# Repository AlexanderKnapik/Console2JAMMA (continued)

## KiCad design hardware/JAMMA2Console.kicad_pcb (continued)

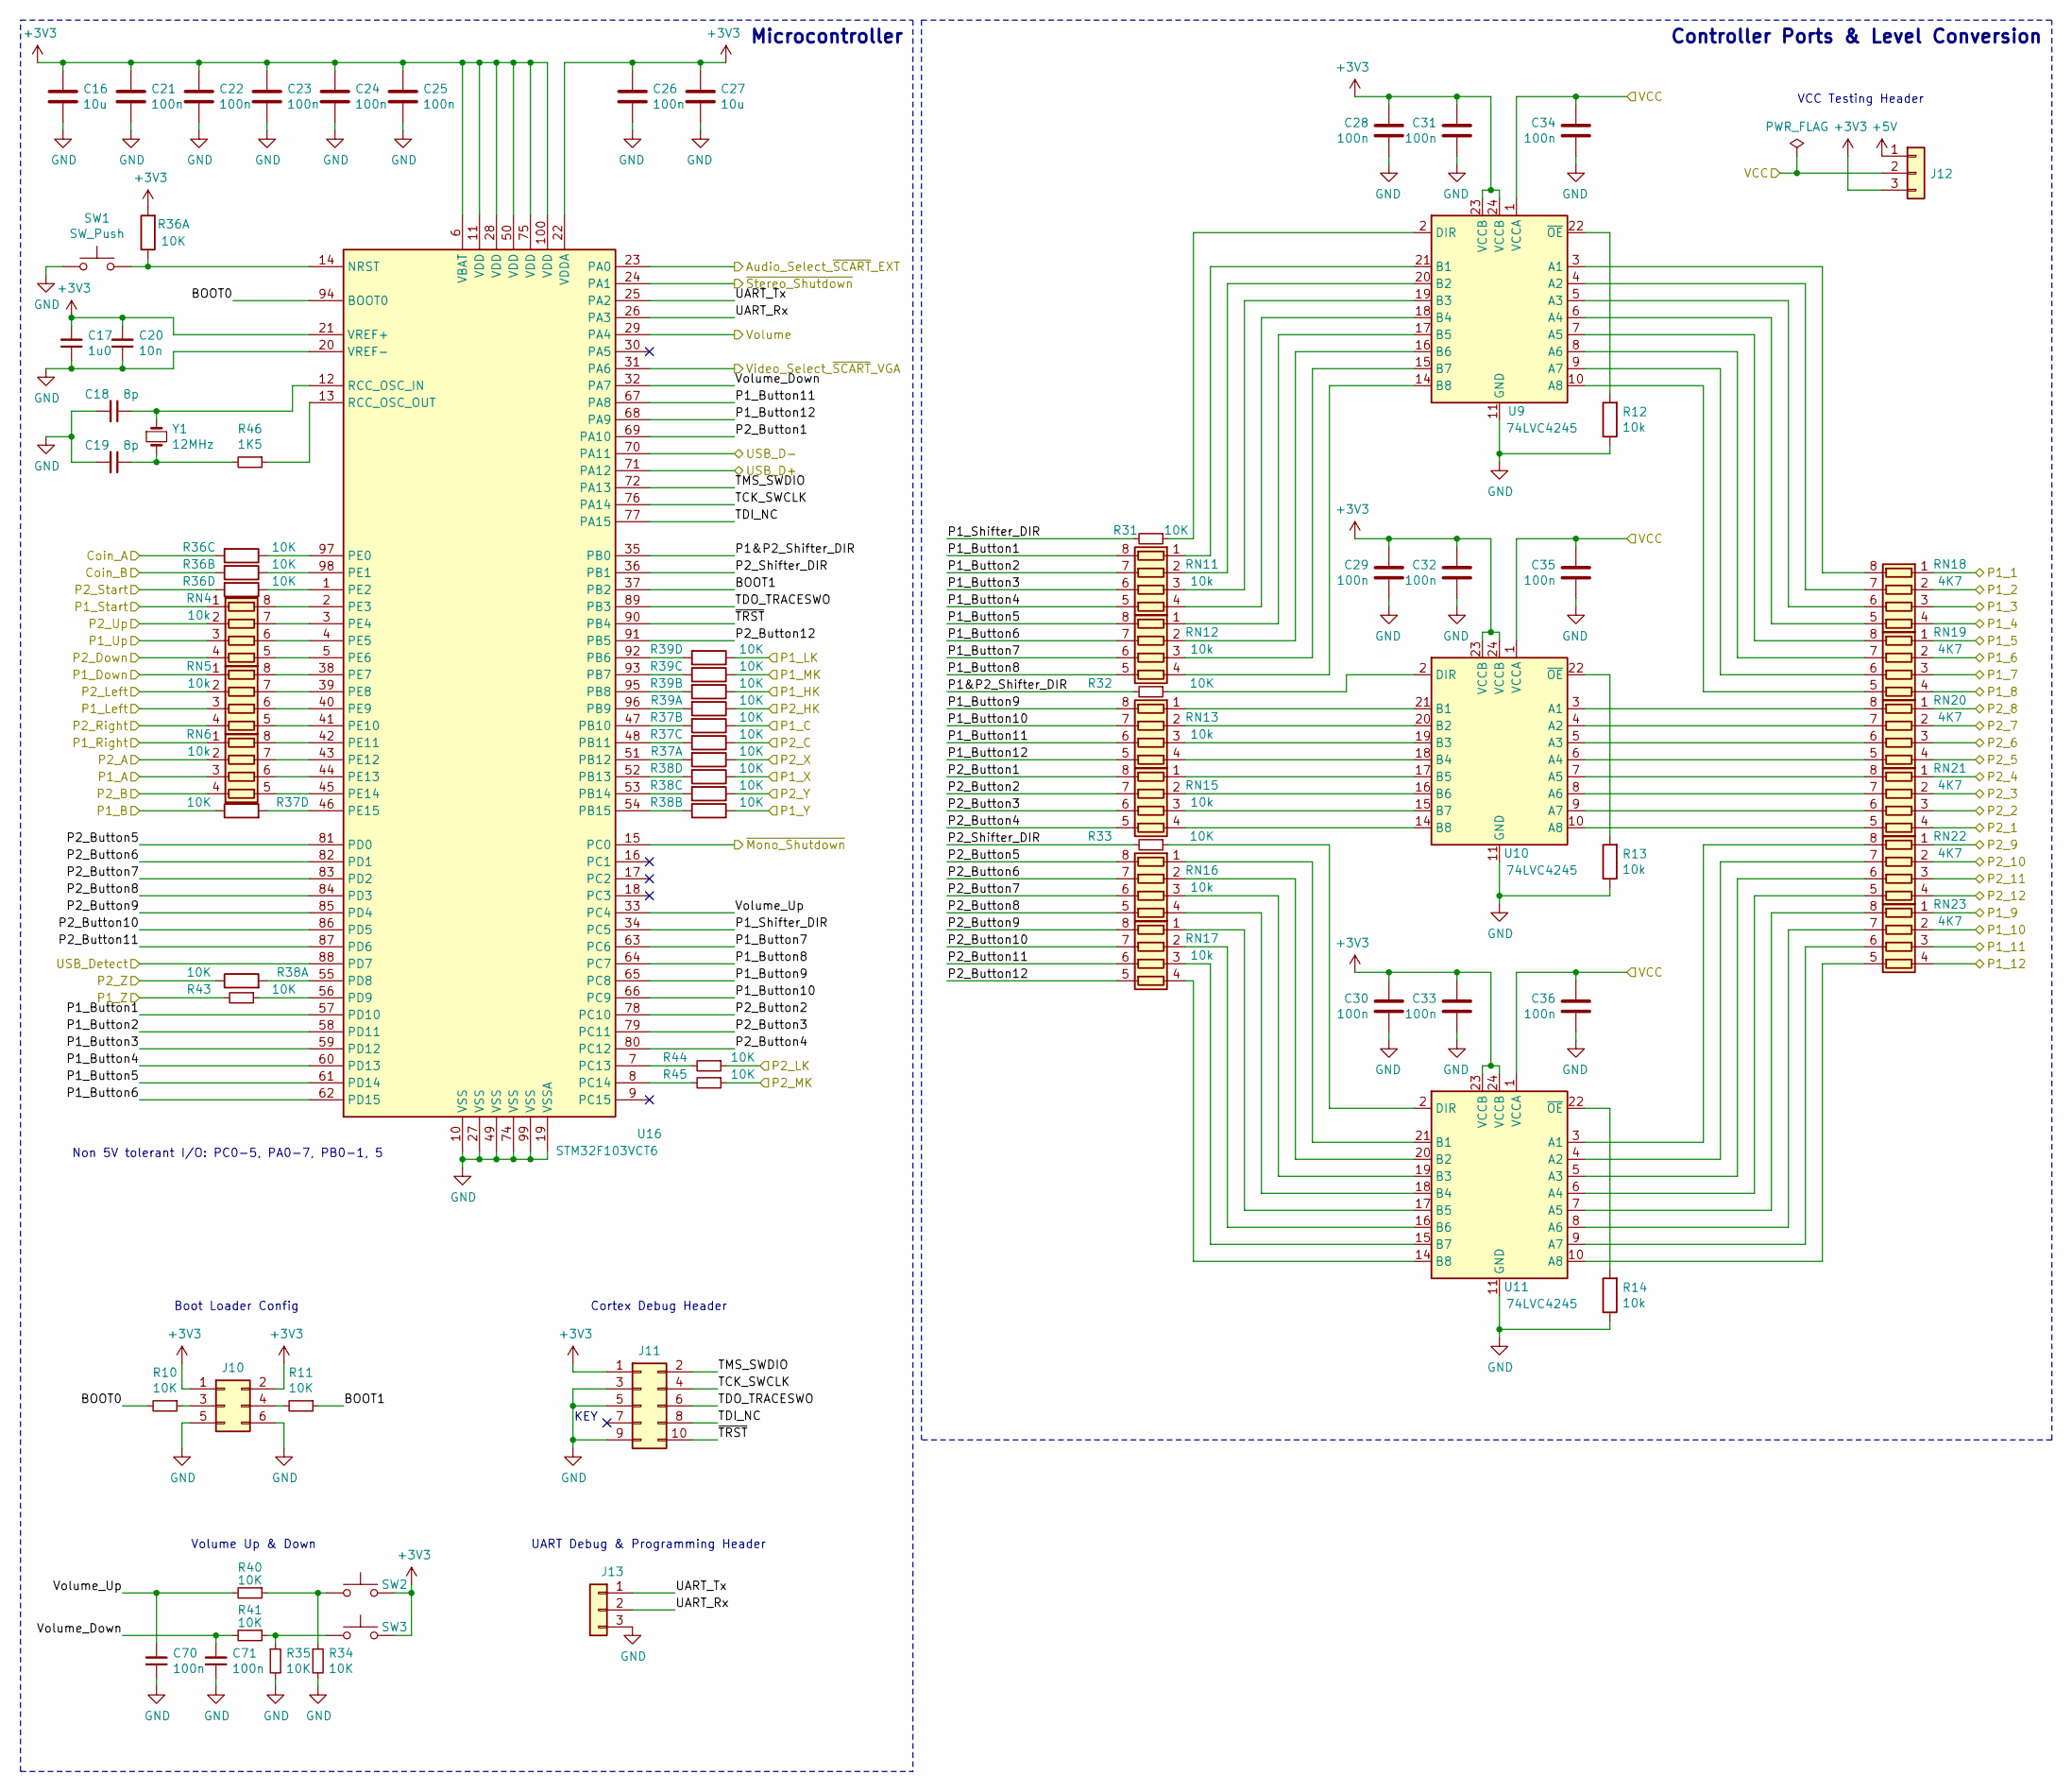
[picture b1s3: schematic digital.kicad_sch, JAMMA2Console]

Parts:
C16, C27: 10u; C_0805_2012Metric
C17: 1u0; C_0603_1608Metric
C18, C19: 8p; C_0603_1608Metric
C20: 10n; C_0603_1608Metric
C21, C22, C23, C24, C25, C26, C28, C29, C30, C31, C32, C33, C34, C35, C36, C70, C71: 100n; C_0603_1608Metric
J10: Conn_02x03_Odd_Even; PinHeader_2x03_P2.54mm_Vertical_SMD
J11: Conn_02x05_Odd_Even; PinHeader_2x05_P1.27mm_Vertical_SMD
J12, J13: Conn_01x03; PinHeader_1x03_P2.54mm_Vertical
R10, R11, R31, R32, R33, R34, R35, R40, R41, R43, R44, R45: 10K; R_0603_1608Metric
R12, R13, R14: 10k; R_0603_1608Metric
R36, R37, R38, R39: 10K; R_Array_Convex_4x0603
R46: 1K5; R_0603_1608Metric
RN4, RN5, RN6, RN11, RN12, RN13, RN15, RN16, RN17: 10k; R_Array_Convex_4x0603
RN18, RN19, RN20, RN21, RN22, RN23: 4K7; R_Array_Convex_4x0603
SW1, SW2, SW3: SW_Push; SW_Push_SPST_NO_Alps_SKRP
U9, U10, U11: 74LVC4245; TSSOP-24_4.4x7.8mm_P0.65mm
U16: STM32F103VCT6; LQFP-100_14x14mm_P0.5mm
Y1: 12MHz; Crystal_SMD_5032-2Pin_5.0x3.2mm

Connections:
+3V3: C16.1, C17.2, C20.2, C21.1, C22.1, C23.1, C24.1, C25.1, C26.1, C27.1, C28.1, C29.1, C30.1, C31.1, C32.1, C33.1, J10.1, J10.2, J11.1, J12.3, R36.1, SW2.2, SW3.2, U9.23 (VCCB), U9.24 (VCCB), U10.23 (VCCB), U10.24 (VCCB), U11.23 (VCCB), U11.24 (VCCB), U16.6 (VBAT), U16.11 (VDD), U16.21 (VREF+), U16.22 (VDDA), U16.28 (VDD), U16.50 (VDD), U16.75 (VDD), U16.100 (VDD); also elsewhere on the board
+5V: J12.1; also elsewhere on the board
/Audio_Select_~SCART~_EXT: U16.23 (PA0); also elsewhere on the board
/Coin_A: R36.3; also elsewhere on the board
/Coin_B: R36.2; also elsewhere on the board
/Digital I/O/BOOT0: R10.2, U16.94 (BOOT0)
/Digital I/O/BOOT1: R11.1, U16.37 (PB2)
/Digital I/O/P1&P2_Shifter_DIR: R32.2, U16.35 (PB0)
/Digital I/O/P1_Button1: RN11.8 (R1.2), U16.57 (PD10)
/Digital I/O/P1_Button2: RN11.7 (R2.2), U16.58 (PD11)
/Digital I/O/P1_Button3: RN11.6 (R3.2), U16.59 (PD12)
/Digital I/O/P1_Button4: RN11.5 (R4.2), U16.60 (PD13)
/Digital I/O/P1_Button5: RN12.8 (R1.2), U16.61 (PD14)
/Digital I/O/P1_Button6: RN12.7 (R2.2), U16.62 (PD15)
/Digital I/O/P1_Button7: RN12.6 (R3.2), U16.63 (PC6)
/Digital I/O/P1_Button8: RN12.5 (R4.2), U16.64 (PC7)
/Digital I/O/P1_Button9: RN13.8 (R1.2), U16.65 (PC8)
/Digital I/O/P1_Button10: RN13.7 (R2.2), U16.66 (PC9)
/Digital I/O/P1_Button11: RN13.6 (R3.2), U16.67 (PA8)
/Digital I/O/P1_Button12: RN13.5 (R4.2), U16.68 (PA9)
/Digital I/O/P1_Shifter_DIR: R31.2, U16.34 (PC5)
/Digital I/O/P2_Button1: RN15.8 (R1.2), U16.69 (PA10)
/Digital I/O/P2_Button2: RN15.7 (R2.2), U16.78 (PC10)
/Digital I/O/P2_Button3: RN15.6 (R3.2), U16.79 (PC11)
/Digital I/O/P2_Button4: RN15.5 (R4.2), U16.80 (PC12)
/Digital I/O/P2_Button5: RN16.8 (R1.2), U16.81 (PD0)
/Digital I/O/P2_Button6: RN16.7 (R2.2), U16.82 (PD1)
/Digital I/O/P2_Button7: RN16.6 (R3.2), U16.83 (PD2)
/Digital I/O/P2_Button8: RN16.5 (R4.2), U16.84 (PD3)
/Digital I/O/P2_Button9: RN17.8 (R1.2), U16.85 (PD4)
/Digital I/O/P2_Button10: RN17.7 (R2.2), U16.86 (PD5)
/Digital I/O/P2_Button11: RN17.6 (R3.2), U16.87 (PD6)
/Digital I/O/P2_Button12: RN17.5 (R4.2), U16.91 (PB5)
/Digital I/O/P2_Shifter_DIR: R33.2, U16.36 (PB1)
/Digital I/O/TCK_SWCLK: J11.4, U16.76 (PA14)
/Digital I/O/TDI_NC: J11.8, U16.77 (PA15)
/Digital I/O/TDO_TRACESWO: J11.6, U16.89 (PB3)
/Digital I/O/TMS_SWDIO: J11.2, U16.72 (PA13)
/Digital I/O/UART_Rx: J13.2, U16.26 (PA3)
/Digital I/O/UART_Tx: J13.1, U16.25 (PA2)
/Digital I/O/Volume_Down: C71.2, R41.2, U16.32 (PA7)
/Digital I/O/Volume_Up: C70.2, R40.2, U16.33 (PC4)
/Digital I/O/~TRST~: J11.10, U16.90 (PB4)
/P1_1: RN18.1 (R1.1); also elsewhere on the board
/P1_2: RN18.2 (R2.1); also elsewhere on the board
/P1_3: RN18.3 (R3.1); also elsewhere on the board
/P1_4: RN18.4 (R4.1); also elsewhere on the board
/P1_5: RN19.1 (R1.1); also elsewhere on the board
/P1_6: RN19.2 (R2.1); also elsewhere on the board
/P1_7: RN19.3 (R3.1); also elsewhere on the board
/P1_8: RN19.4 (R4.1); also elsewhere on the board
/P1_9: RN23.1 (R1.1); also elsewhere on the board
/P1_10: RN23.2 (R2.1); also elsewhere on the board
/P1_11: RN23.3 (R3.1); also elsewhere on the board
/P1_12: RN23.4 (R4.1); also elsewhere on the board
/P1_A: RN6.3 (R3.1); also elsewhere on the board
/P1_B: R37.5; also elsewhere on the board
/P1_C: R37.7; also elsewhere on the board
/P1_Down: RN5.1 (R1.1); also elsewhere on the board
/P1_HK: R39.7; also elsewhere on the board
/P1_LK: R39.5; also elsewhere on the board
/P1_Left: RN5.3 (R3.1); also elsewhere on the board
/P1_MK: R39.6; also elsewhere on the board
/P1_Right: RN6.1 (R1.1); also elsewhere on the board
/P1_Start: RN4.1 (R1.1); also elsewhere on the board
/P1_Up: RN4.3 (R3.1); also elsewhere on the board
/P1_X: R38.5; also elsewhere on the board
/P1_Y: R38.7; also elsewhere on the board
/P1_Z: R43.2; also elsewhere on the board
/P2_1: RN21.4 (R4.1); also elsewhere on the board
/P2_2: RN21.3 (R3.1); also elsewhere on the board
/P2_3: RN21.2 (R2.1); also elsewhere on the board
/P2_4: RN21.1 (R1.1); also elsewhere on the board
/P2_5: RN20.4 (R4.1); also elsewhere on the board
/P2_6: RN20.3 (R3.1); also elsewhere on the board
/P2_7: RN20.2 (R2.1); also elsewhere on the board
/P2_8: RN20.1 (R1.1); also elsewhere on the board
/P2_9: RN22.1 (R1.1); also elsewhere on the board
/P2_10: RN22.2 (R2.1); also elsewhere on the board
/P2_11: RN22.3 (R3.1); also elsewhere on the board
/P2_12: RN22.4 (R4.1); also elsewhere on the board
/P2_A: RN6.2 (R2.1); also elsewhere on the board
/P2_B: RN6.4 (R4.1); also elsewhere on the board
/P2_C: R37.6; also elsewhere on the board
/P2_Down: RN4.4 (R4.1); also elsewhere on the board
/P2_HK: R39.8; also elsewhere on the board
/P2_LK: R44.1; also elsewhere on the board
/P2_Left: RN5.2 (R2.1); also elsewhere on the board
/P2_MK: R45.1; also elsewhere on the board
/P2_Right: RN5.4 (R4.1); also elsewhere on the board
/P2_Start: R36.4; also elsewhere on the board
/P2_Up: RN4.2 (R2.1); also elsewhere on the board
/P2_X: R37.8; also elsewhere on the board
/P2_Y: R38.6; also elsewhere on the board
/P2_Z: R38.8; also elsewhere on the board
/USB_D+: U16.71 (PA12); also elsewhere on the board
/USB_D-: U16.70 (PA11); also elsewhere on the board
/USB_Detect: U16.88 (PD7); also elsewhere on the board
/VCC: C34.1, C35.1, C36.1, J12.2, U9.1 (VCCA), U10.1 (VCCA), U11.1 (VCCA); also elsewhere on the board
/Video_Select_~SCART~_VGA: U16.31 (PA6); also elsewhere on the board
/Volume: U16.29 (PA4); also elsewhere on the board
/~Mono_Shutdown~: U16.15 (PC0); also elsewhere on the board
/~Stereo_Shutdown~: U16.24 (PA1); also elsewhere on the board
GND: C16.2, C17.1, C18.2, C19.2, C20.1, C21.2, C22.2, C23.2, C24.2, C25.2, C26.2, C27.2, C28.2, C29.2, C30.2, C31.2, C32.2, C33.2, C34.2, C35.2, C36.2, C70.1, C71.1, J10.5, J10.6, J11.3, J11.5, J11.9, J13.3, R12.1, R13.1, R14.1, R34.2, R35.2, SW1.1, U9.11 (GND), U9.12 (GND), U9.13 (GND), U10.11 (GND), U10.12 (GND), U10.13 (GND), U11.11 (GND), U11.12 (GND), U11.13 (GND), U16.10 (VSS), U16.19 (VSSA), U16.20 (VREF-), U16.27 (VSS), U16.49 (VSS), U16.74 (VSS), U16.99 (VSS); also elsewhere on the board
unnamed: C18.1, U16.12 (RCC_OSC_IN), Y1.1
unnamed: C19.1, R46.2, Y1.2
unnamed: J10.3, R10.1
unnamed: J10.4, R11.2
unnamed: R12.2, U9.22 (~OE)
unnamed: R13.2, U10.22 (~OE)
unnamed: R14.2, U11.22 (~OE)
unnamed: R31.1, U9.2 (DIR)
unnamed: R32.1, U10.2 (DIR)
unnamed: R33.1, U11.2 (DIR)
unnamed: R34.1, R40.1, SW2.1
unnamed: R35.1, R41.1, SW3.1
unnamed: R36.5, U16.1 (PE2)
unnamed: R36.6, U16.97 (PE0)
unnamed: R36.7, U16.98 (PE1)
unnamed: R36.8, SW1.2, U16.14 (NRST)
unnamed: R37.1, U16.51 (PB12)
unnamed: R37.2, U16.47 (PB10)
unnamed: R37.3, U16.48 (PB11)
unnamed: R37.4, U16.46 (PE15)
unnamed: R38.1, U16.55 (PD8)
unnamed: R38.2, U16.54 (PB15)
unnamed: R38.3, U16.53 (PB14)
unnamed: R38.4, U16.52 (PB13)
unnamed: R39.1, U16.96 (PB9)
unnamed: R39.2, U16.95 (PB8)
unnamed: R39.3, U16.93 (PB7)
unnamed: R39.4, U16.92 (PB6)
unnamed: R43.1, U16.56 (PD9)
unnamed: R44.2, U16.7 (PC13)
unnamed: R45.2, U16.8 (PC14)
unnamed: R46.1, U16.13 (RCC_OSC_OUT)
unnamed: RN4.5 (R4.2), U16.5 (PE6)
unnamed: RN4.6 (R3.2), U16.4 (PE5)
unnamed: RN4.7 (R2.2), U16.3 (PE4)
unnamed: RN4.8 (R1.2), U16.2 (PE3)
unnamed: RN5.5 (R4.2), U16.41 (PE10)
unnamed: RN5.6 (R3.2), U16.40 (PE9)
unnamed: RN5.7 (R2.2), U16.39 (PE8)
unnamed: RN5.8 (R1.2), U16.38 (PE7)
unnamed: RN6.5 (R4.2), U16.45 (PE14)
unnamed: RN6.6 (R3.2), U16.44 (PE13)
unnamed: RN6.7 (R2.2), U16.43 (PE12)
unnamed: RN6.8 (R1.2), U16.42 (PE11)
unnamed: RN11.1 (R1.1), U9.21 (B1)
unnamed: RN11.2 (R2.1), U9.20 (B2)
unnamed: RN11.3 (R3.1), U9.19 (B3)
unnamed: RN11.4 (R4.1), U9.18 (B4)
unnamed: RN12.1 (R1.1), U9.17 (B5)
unnamed: RN12.2 (R2.1), U9.16 (B6)
unnamed: RN12.3 (R3.1), U9.15 (B7)
unnamed: RN12.4 (R4.1), U9.14 (B8)
unnamed: RN13.1 (R1.1), U10.21 (B1)
unnamed: RN13.2 (R2.1), U10.20 (B2)
unnamed: RN13.3 (R3.1), U10.19 (B3)
unnamed: RN13.4 (R4.1), U10.18 (B4)
unnamed: RN15.1 (R1.1), U10.17 (B5)
unnamed: RN15.2 (R2.1), U10.16 (B6)
unnamed: RN15.3 (R3.1), U10.15 (B7)
unnamed: RN15.4 (R4.1), U10.14 (B8)
unnamed: RN16.1 (R1.1), U11.21 (B1)
unnamed: RN16.2 (R2.1), U11.20 (B2)
unnamed: RN16.3 (R3.1), U11.19 (B3)
unnamed: RN16.4 (R4.1), U11.18 (B4)
unnamed: RN17.1 (R1.1), U11.17 (B5)
unnamed: RN17.2 (R2.1), U11.16 (B6)
unnamed: RN17.3 (R3.1), U11.15 (B7)
unnamed: RN17.4 (R4.1), U11.14 (B8)
unnamed: RN18.5 (R4.2), U9.6 (A4)
unnamed: RN18.6 (R3.2), U9.5 (A3)
unnamed: RN18.7 (R2.2), U9.4 (A2)
unnamed: RN18.8 (R1.2), U9.3 (A1)
unnamed: RN19.5 (R4.2), U9.10 (A8)
unnamed: RN19.6 (R3.2), U9.9 (A7)
unnamed: RN19.7 (R2.2), U9.8 (A6)
unnamed: RN19.8 (R1.2), U9.7 (A5)
unnamed: RN20.5 (R4.2), U10.6 (A4)
unnamed: RN20.6 (R3.2), U10.5 (A3)
unnamed: RN20.7 (R2.2), U10.4 (A2)
unnamed: RN20.8 (R1.2), U10.3 (A1)
unnamed: RN21.5 (R4.2), U10.10 (A8)
unnamed: RN21.6 (R3.2), U10.9 (A7)
unnamed: RN21.7 (R2.2), U10.8 (A6)
unnamed: RN21.8 (R1.2), U10.7 (A5)
unnamed: RN22.5 (R4.2), U11.6 (A4)
unnamed: RN22.6 (R3.2), U11.5 (A3)
unnamed: RN22.7 (R2.2), U11.4 (A2)
unnamed: RN22.8 (R1.2), U11.3 (A1)
unnamed: RN23.5 (R4.2), U11.10 (A8)
unnamed: RN23.6 (R3.2), U11.9 (A7)
unnamed: RN23.7 (R2.2), U11.8 (A6)
unnamed: RN23.8 (R1.2), U11.7 (A5)

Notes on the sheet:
Non 5V tolerant I/O: PC0-5, PA0-7, PB0-1, 5
Boot Loader Config
Volume Up & Down
UART Debug & Programming Header
Cortex Debug Header
KEY
Microcontroller
VCC Testing Header
Controller Ports & Level Conversion

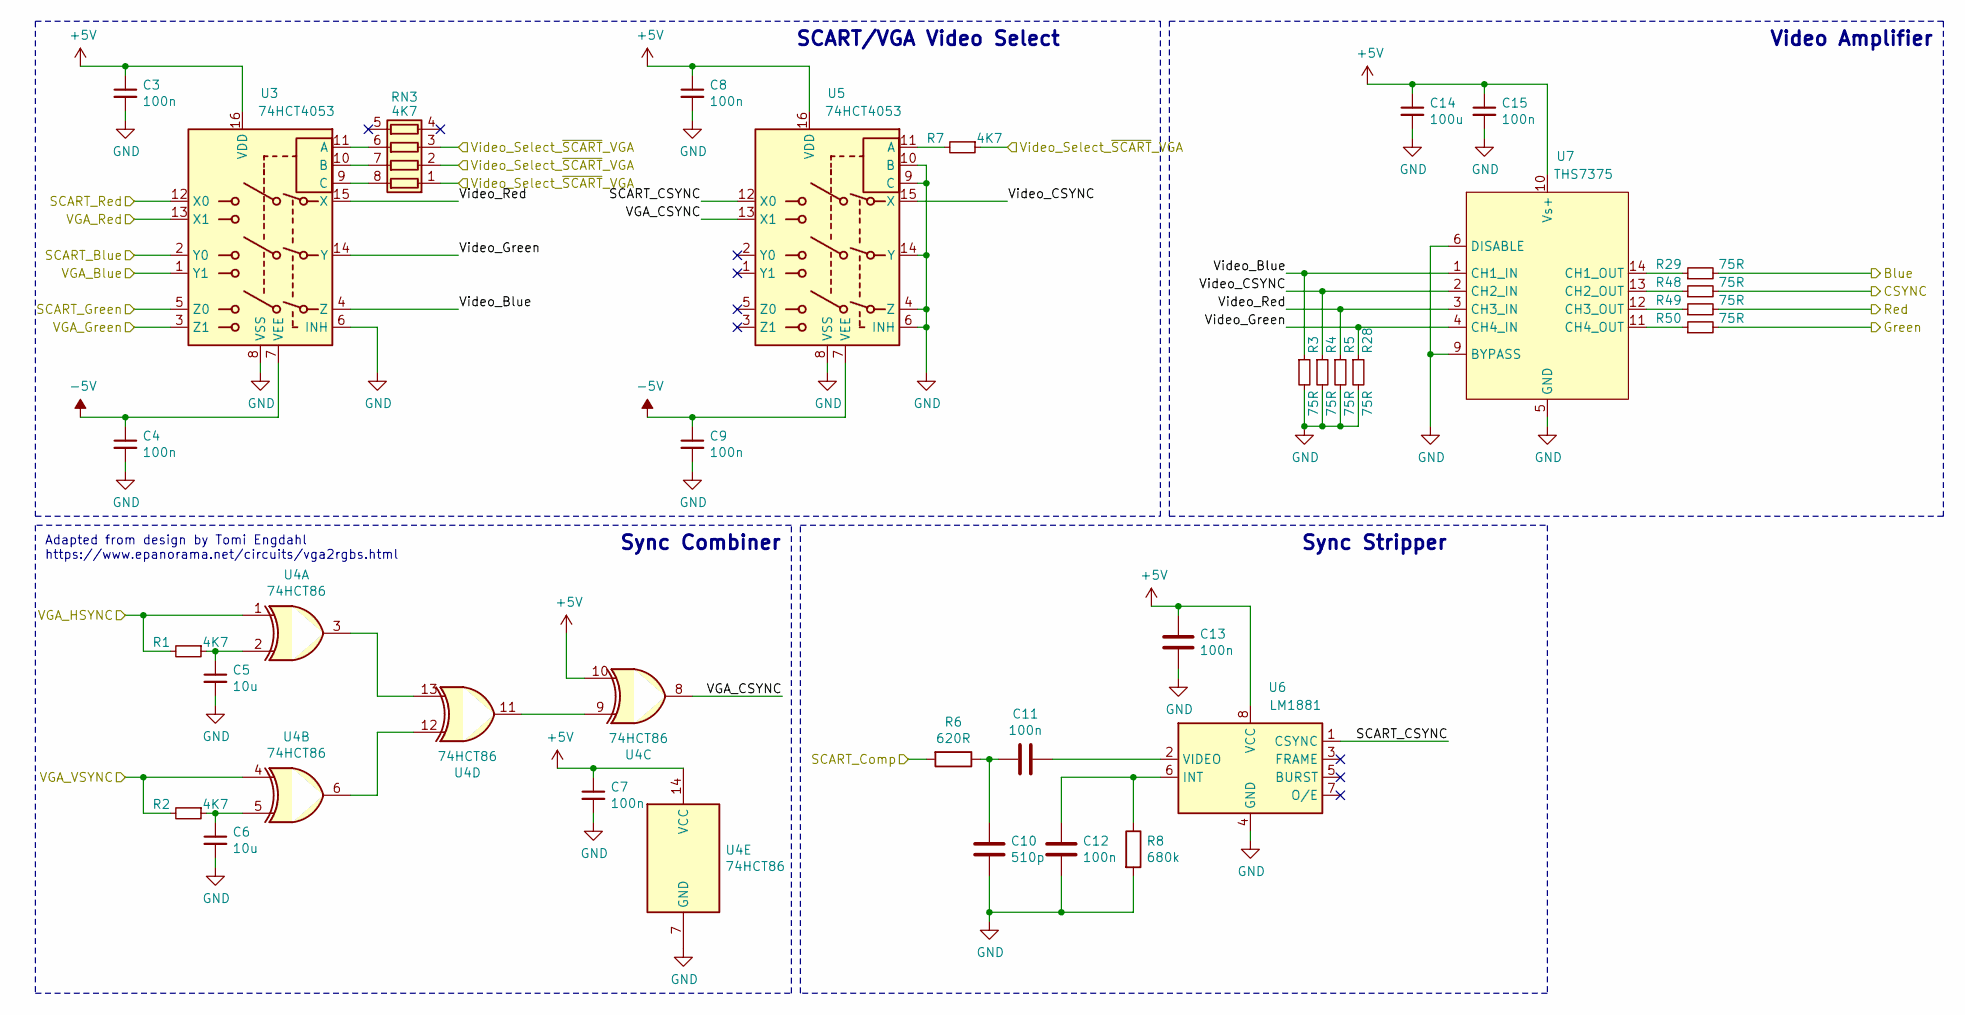
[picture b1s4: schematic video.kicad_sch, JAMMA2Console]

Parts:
C3, C4, C7, C8, C9, C11, C12, C13, C15: 100n; C_0603_1608Metric
C5, C6: 10u; C_0805_2012Metric
C10: 510p; C_0603_1608Metric
C14: 100u; C_1210_3225Metric
R1, R2, R7: 4K7; R_0603_1608Metric
R3, R4, R5, R28, R29, R48, R49, R50: 75R; R_0603_1608Metric
R6: 620R; R_0603_1608Metric
R8: 680k; R_0603_1608Metric
RN3: 4K7; R_Array_Convex_4x0603
U3, U5: 74HCT4053; SSOP-16_5.3x6.2mm_P0.65mm
U4: 74HCT86; SOIC-14_3.9x8.7mm_P1.27mm
U6: LM1881; SOIC-8_3.9x4.9mm_P1.27mm
U7: THS7375; TSSOP-14_4.4x5mm_P0.65mm

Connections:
+5V: C3.1, C7.1, C8.1, C13.1, C14.1, C15.1, U3.16 (VDD), U4.10, U4.14 (VCC), U5.16 (VDD), U6.8 (VCC), U7.10 (Vs+); also elsewhere on the board
-5V: C4.1, C9.1, U3.7 (VEE), U5.7 (VEE); also elsewhere on the board
/Composite_Sync: R48.2; also elsewhere on the board
/SCART_Blue: U3.2 (Y0); also elsewhere on the board
/SCART_Comp: R6.2; also elsewhere on the board
/SCART_Green: U3.5 (Z0); also elsewhere on the board
/SCART_Red: U3.12 (X0); also elsewhere on the board
/VGA_Blue: U3.1 (Y1); also elsewhere on the board
/VGA_Green: U3.3 (Z1); also elsewhere on the board
/VGA_HSYNC: R1.2, U4.1; also elsewhere on the board
/VGA_Red: U3.13 (X1); also elsewhere on the board
/VGA_VSYNC: R2.2, U4.4; also elsewhere on the board
/Video/SCART_CSYNC: U5.12 (X0), U6.1 (CSYNC)
/Video/VGA_CSYNC: U4.8, U5.13 (X1)
/Video/Video_Blue: R3.1, U3.4 (Z), U7.1 (CH1_IN)
/Video/Video_CSYNC: R4.1, U5.15 (X), U7.2 (CH2_IN)
/Video/Video_Green: R28.1, U3.14 (Y), U7.4 (CH4_IN)
/Video/Video_Red: R5.1, U3.15 (X), U7.3 (CH3_IN)
/Video_Blue: R29.2; also elsewhere on the board
/Video_Green: R50.2; also elsewhere on the board
/Video_Red: R49.2; also elsewhere on the board
/Video_Select_~SCART~_VGA: R7.1, RN3.1 (R1.1), RN3.2 (R2.1), RN3.3 (R3.1); also elsewhere on the board
GND: C3.2, C4.2, C5.2, C6.2, C7.2, C8.2, C9.2, C10.2, C12.2, C13.2, C14.2, C15.2, R3.2, R4.2, R5.2, R8.2, R28.2, U3.6 (INH), U3.8 (VSS), U4.7 (GND), U5.4 (Z), U5.6 (INH), U5.8 (VSS), U5.9 (C), U5.10 (B), U5.14 (Y), U6.4 (GND), U7.5 (GND), U7.6 (DISABLE), U7.9 (BYPASS); also elsewhere on the board
unnamed: C5.1, R1.1, U4.2
unnamed: C6.1, R2.1, U4.5
unnamed: C10.1, C11.2, R6.1
unnamed: C11.1, U6.2 (VIDEO)
unnamed: C12.1, R8.1, U6.6 (INT)
unnamed: R7.2, U5.11 (A)
unnamed: R29.1, U7.14 (CH1_OUT)
unnamed: R48.1, U7.13 (CH2_OUT)
unnamed: R49.1, U7.12 (CH3_OUT)
unnamed: R50.1, U7.11 (CH4_OUT)
unnamed: RN3.6 (R3.2), U3.11 (A)
unnamed: RN3.7 (R2.2), U3.10 (B)
unnamed: RN3.8 (R1.2), U3.9 (C)
unnamed: U4.9, U4.11
unnamed: U4.6, U4.12
unnamed: U4.3, U4.13

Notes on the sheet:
Adapted from design by Tomi Engdahl https://www.epanorama.net/circuits/vga2rgbs.html
Sync Combiner
SCART/VGA Video Select
Sync Stripper
Video Amplifier

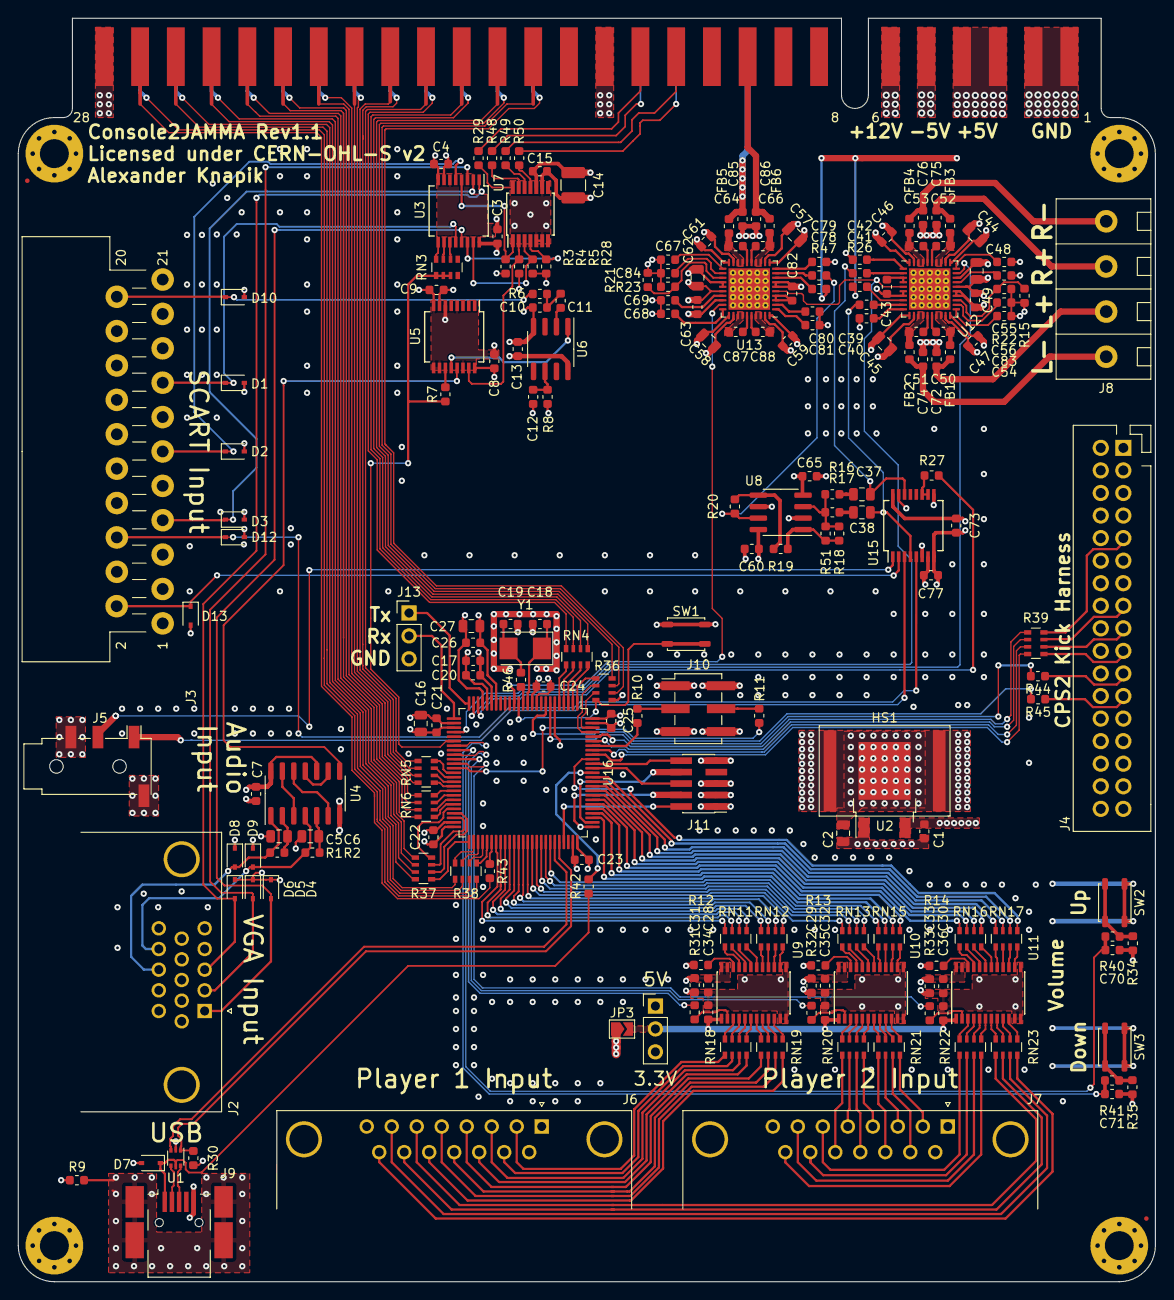
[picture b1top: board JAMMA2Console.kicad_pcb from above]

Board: 4 copper layers, 126.0 x 140.0 mm, 211 parts (0 on the bottom side), 295 nets.

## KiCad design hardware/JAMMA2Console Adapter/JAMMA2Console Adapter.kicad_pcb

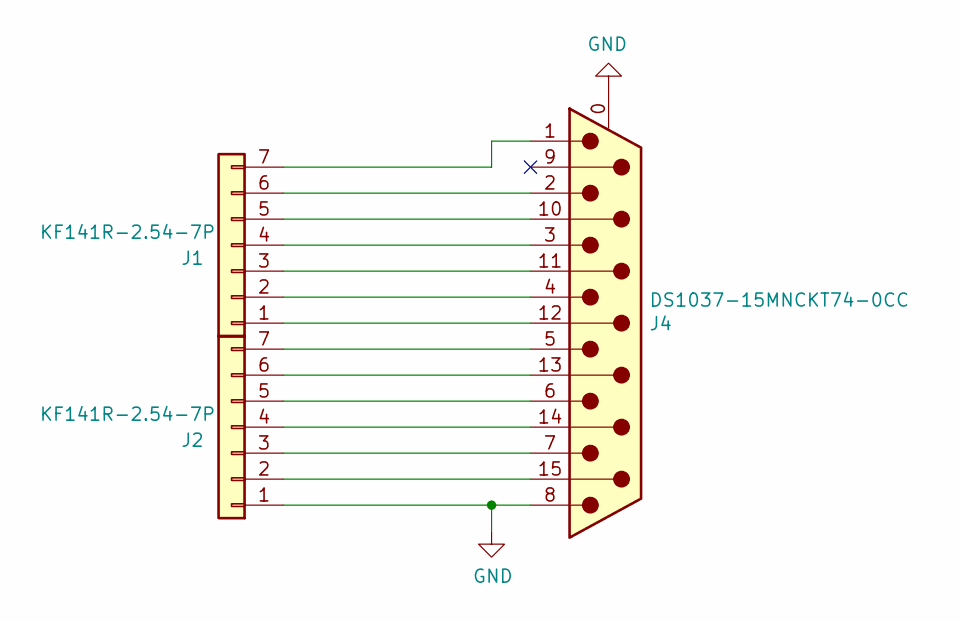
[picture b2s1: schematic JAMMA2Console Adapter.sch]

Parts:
J1, J2: KF141R-2.54-7P; CixiKefa_KF141R-2.54-7P_1x7_P2.54mm_Horizontal
J4: DS1037-15MNCKT74-0CC; DSUB-15_Male_Horizontal_P2.77x2.84mm_EdgePinOffset8.10mm_Ho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

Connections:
GND: J2.1, J4.0 (PAD), J4.8
unnamed: J1.1, J4.12
unnamed: J1.2, J4.4
unnamed: J1.3, J4.11 (P111)
unnamed: J1.4, J4.3
unnamed: J1.5, J4.10
unnamed: J1.6, J4.2
unnamed: J1.7, J4.1
unnamed: J2.2, J4.15
unnamed: J2.3, J4.7
unnamed: J2.4, J4.14
unnamed: J2.5, J4.6
unnamed: J2.6, J4.13
unnamed: J2.7, J4.5

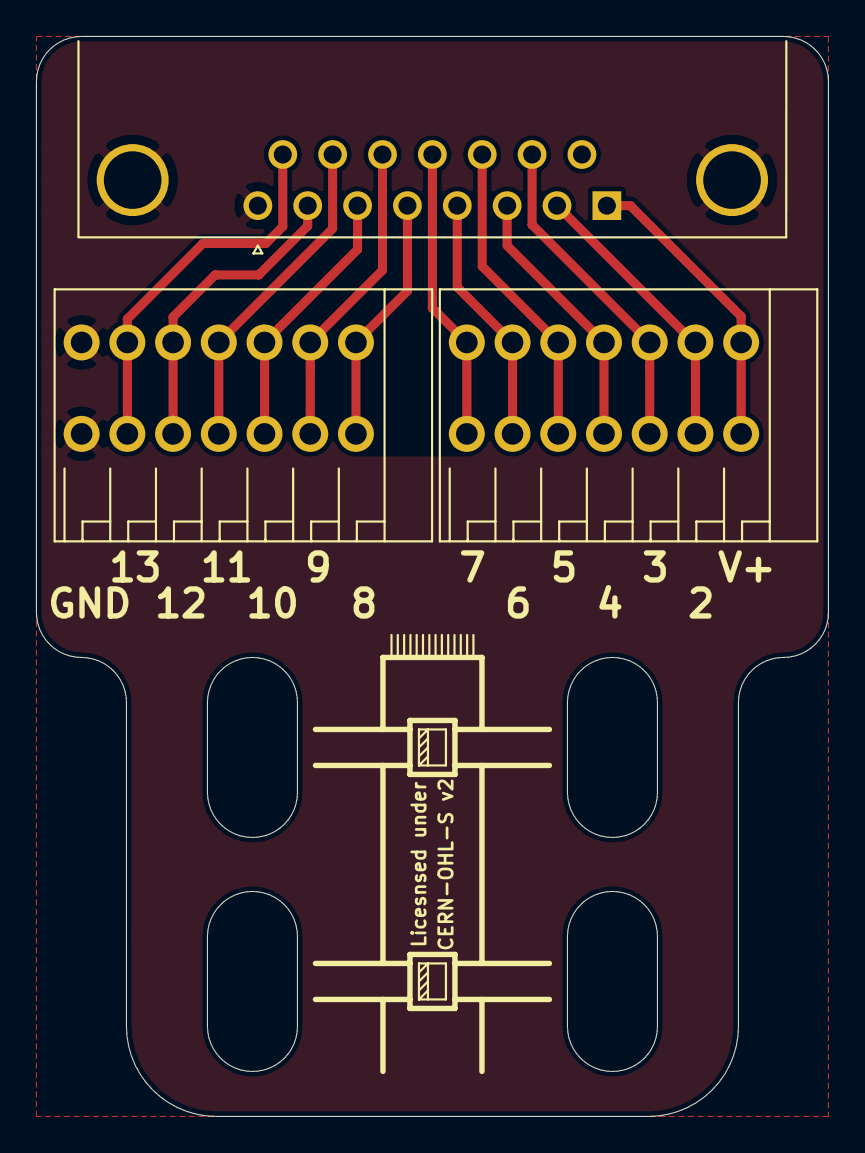
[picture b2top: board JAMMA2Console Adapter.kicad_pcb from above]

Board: 2 copper layers, 44.0 x 60.0 mm, 3 parts (0 on the bottom side), 14 nets.

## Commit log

2019-12-19 Initialising repo
2019-12-28 Updating work so far. Mainly just to set up an online repository for everything, so I can switch to my desktop
2020-02-02 Just updating on how things are going. Its pretty messy at the moment, but in the same time I'm not even close to finishing the schematic. I'm going to split up the schematic into different pages for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
2020-02-29 More work on various schematic files, added footprint for the speaker out terminal connectors.
2020-04-06 Schematic mainly done. Working on PCB layout in isolated blocks.
2020-04-19 Completing the functionality of PCB layout. Require silkscreen placement still, though.
2020-04-21 Updating silkscreen placement and fixing up a few issues with layout. Still require via stitching to be done. Adding CERN OHL S license in hardware folder.
2020-04-26 Completing layout & minor edits for the main PCB. Added a project for the adapters to plug controllers into.
2020-06-04 Started major rework on the Audio section (chose the wrong amplifier as it can't drive 4Ohm loads) Moved over to nightly Kicad v 5.9 versions. Was a mistake to do, but will look into reverting anothe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
2020-06-04 Removing files that will break the project in v5.99 if opened
2020-08-16 Pushing work I did a few months ago and I forgot to push. Identified some mistakes which I'll fix in a future commit.
2020-08-16 Updated the schematic & layout to fix the heat sink net issues with the 3v3 regulator.
2020-08-25 Adding extra info on todo list about USB impedance issues on Rev 1.0
2021-04-27 Adding to the readme file about progress and including pictures.
2021-04-27 Resizing image.
2021-04-27 Updating gitignore for backup files
